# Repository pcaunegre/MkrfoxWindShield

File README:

This project includes several independant modules:

1. the hardware is an Arduino shield compatible with the MKRFOX1200 board.
 The shield provides an interface with wind sensors.
 3 types of wind sensors are compatible with this shield:
 --Davis
 --Peet Bros
 --Shenzen

2. the sofware to run the wind sensor and send measure to the OpenWindMap network

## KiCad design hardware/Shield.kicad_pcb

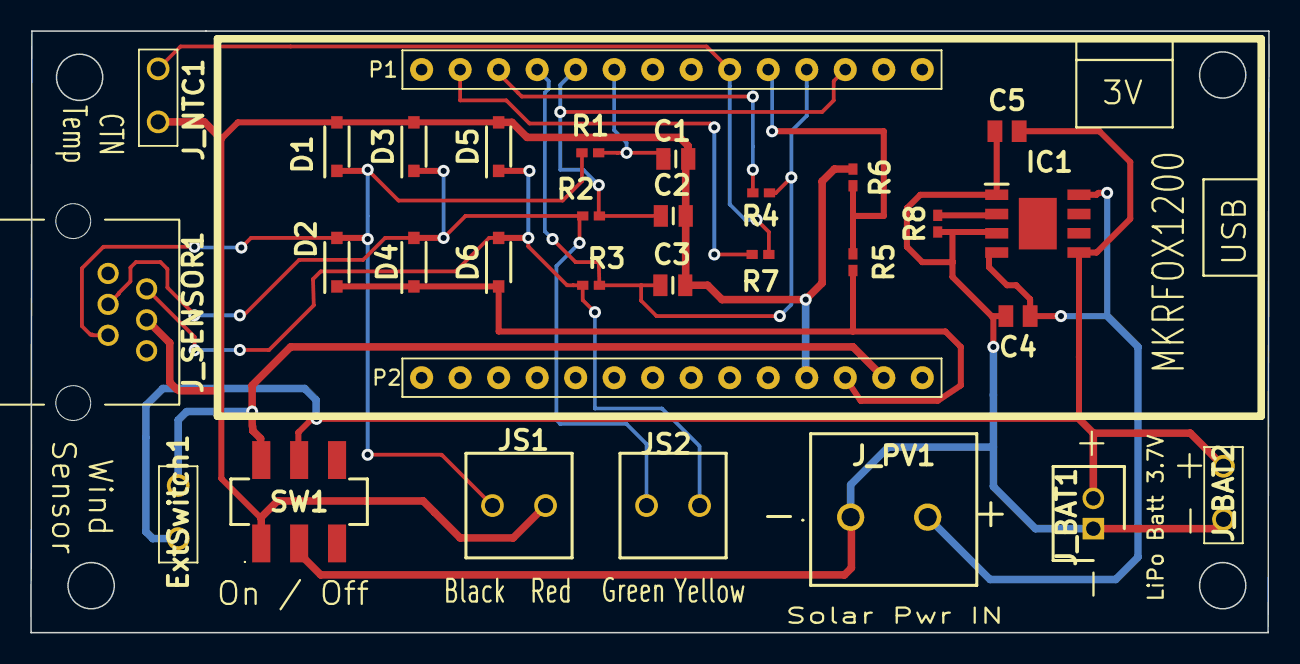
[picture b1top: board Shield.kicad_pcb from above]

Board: 2 copper layers, 81.6 x 39.7 mm, 31 parts (0 on the bottom side), 17 nets.

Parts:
C1, C2, C3: 10n; CAPC2012X65N
C4, C5: 10u; CAPC2012X140N
D1, D2, D3, D4, D5, D6: 1N5819W; SODFL3516X120N
ExtSwitch1: KF350-3.5-2P; SolderPoints
IC1: TP4056-42-ESOP8; SOIC127P600X175-9N
JS1, JS2: KF350-3.5-2P; KF350352P
J_BAT1: PH-2AK; SHDR2W52P0X200_1X2_600X460X630P
J_BAT2: KF350-3.5-2P; SolderPoints
J_NTC1: KF350-3.5-2P; SolderPoints
J_PV1: WJ500V-5.08-2P; WJ500V5082P
J_SENSOR1: DS1133-S60APS; DS1133S60APS
P1: CONN_14_1; CONN14_FP1
P2: CONN_14_2; CONN14_FP2
R1, R2, R3: 1K; RESC1005X40N
R4, R7: 10K; RESC1005X40N
R5: 390k; RESC1005X40N
R6: 100k; RESC1005X40N
R8: 20K; RESC1005X40N
SW1: JS202011SCQN

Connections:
A3: P1.A3, R5.2, R6.1
A4: J_NTC1.1, P1.A4, R7.2
D0: C1.2, P1.0, R1.2
D1A1: C2.2, P1.1, P1.A1, R2.2
D2A2: C3.2, P1.2, P1.A2, R3.2, R4.1
D3: P1.3, R4.2
D4: P1.4, R7.1
GND: C4.1, C5.1, IC1.1, IC1.3, J_BAT1.1, J_BAT2.2, J_PV1.1, R8.1, SW1.2
MGND: C1.1, C2.1, C3.1, D1.2, D3.2, D5.2, JS1.2, J_NTC1.2, J_SENSOR1.3, P2.GND, R6.2, SW1.1
unnamed: IC1.2, R8.2
VBAT: C5.2, ExtSwitch1.2, IC1.5, J_BAT1.2, J_BAT2.1, SW1.5
VCC: D2.1, D4.1, D6.1, P2.VCC, R5.1
VIN: ExtSwitch1.1, P2.VIN, SW1.6
VPV: C4.2, IC1.4, IC1.8, J_PV1.2
Wire1: D1.1, D2.2, JS1.1, J_SENSOR1.2, R1.1
Wire3: D3.1, D4.2, JS2.1, J_SENSOR1.4, R2.1
Wire4: D5.1, D6.2, JS2.2, J_SENSOR1.5, R3.1

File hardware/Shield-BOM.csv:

Comment,Designator,Footprint,LCSC,MFR part,
10nF ?10% 50V,"C1,C2,C3",0805,C1710 ,CL21B103KBANNNC,SMD
10uF ?10% 16V,"C4,C5",0805,C95841,CL21B106KOQNNNE,
Diode schottky 60V 1A ,"D1,D2,D3,D4,D5,D6",SOD-123,C110797,"PMEG6010CEH,115",
TP4056-42-ESOP8,IC1,ESOP-8_EP_3.9x4.9x1.27P,C16581,TP4056-42-ESOP8,
1k ?1% 1/16W,"R1,R2,R3",0402,C11702,0402WGF1001TCE,
10k 1/16W ?1% ,"R4,R7",0402,C25744,0402WGF1002TCE,
390k ?1% 1/16W,R5,0402,C25782,0402WGF3903TCE,
100k 1/16W ?1% ,R6,0402,C25741,0402WGF1003TCE,
20k 1/16W ?1%,R8,0402,C25765,0402WGF2002TCE,
Switch 6V 300mA ,SW1,SMD,C221666,JS202011SCQN,
P=3.5mm Screw terminal,"JS1,JS2",CONN-TH_P3.50_KF350-3.5-2P,C474892,KF350-3.5-2P,Hand soldered
2.54mm 14 Straight 1 Receptacle Through Hole,"P1,P2",HDR-TH_14P-P2.54-V,C124407,B-2200S14P-A120,
"2 Header PH 0.079""(2.00mm) Male Pin Through Hole Wire To Board",J_BAT1,CONN-TH_PH-2A,C8886,PH-2AK,
P=5.08mm Screw terminal ,J_PV1,CONN-TH_2P-P5.00_WJ500V-5.08-2P,C8465,WJ500V-5.08-2P,
DS1133-S60APS,J_SENSOR1,RJ11-TH_PCB-6P6C-90,C77857,DS1133-S60APS,
,,,,,
,J_NTC1,not mounted !!!,,,Not mounted

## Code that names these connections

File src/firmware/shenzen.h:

#define SHENZEN 30         // sensor number

#define ShenzenWire1  0    // wire1 (Black) to digital 0
//      ShenzenWire2       // wire2 (Red) to GND
#define ShenzenWire3  1    // wire3 (Yellow) to digital 1
#define ShenzenWire4  2    // wire4 (Green) to digital 2


#define ShenzenDirPin   A2  // analog direction - wire4 (Green)
#define ShenzenSpeedPin 1   // dig speed on D1  - wire3 (Yellow)

void Shenzen_setup();
void Shenzen_isr_speed();
int  Shenzen_takeWspeed(int deltaT);
int  Shenzen_takeWdir();

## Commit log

2021-11-05 project init
2021-11-07 measure working with davis
2021-11-08 shenzen sensor ok
2021-11-10 added sensor detection
2021-11-10 split code in several files
2021-11-15 parametrised thresholds
2021-11-18 started readme
2021-11-18 tuned detection, working for shenzen
2021-11-19 added peet, but not tested
2021-11-26 added vbat measure
2021-11-29 controling sensor power to save current
2021-11-29 added admin reccurent action
2021-12-01 preparing admin message
2021-12-01 created hardware schematics, started pcb
2021-12-02 completed PCB, DRC OK
2021-12-02 deleted unneeded file
2021-12-03 added grounded backplane
2021-12-03 fixed holes position
2021-12-03 added JLCPCB BOM file
2021-12-07 changed diode ref because missing in fab catalog
2021-12-21 validated sigfox dispatch, validated I consumption
2022-01-18 finished sensors, temperature, admin report
2022-01-18 doc added
2022-01-18 manual added
2022-01-19 revised manual
2022-01-20 more documentation
2022-01-20 minor doc details
2022-03-24 changed power on Davis, added debug control from pin11
2022-04-07 manual revised after code revision
2022-04-07 added usb serial reader python script
2022-04-13 fixed terrific bug on wind dir with Davis or Misol
2022-04-13 updated soft version
2022-04-21 reorg sockets
2022-04-21 Revert "updated soft version"
    This reverts commit ec333ab792278aeebab38000c117c2b14d257bda.
2022-04-22 modified hardware: position of sockets, points for external switch
2022-04-22 put the right code version
2022-05-04 doc update wrt hardware change
2022-10-28 little change to avoid compiler warning on char declaration
2022-11-08 fix timing overflow due to var type, added debug infos
2022-11-09 some code clean up
2022-11-21 utilities for getting admin report from OWM
2022-11-22 trying to fix admin report dispatch
2022-12-12 more printing features added to getAdminReport.py
2022-12-20 changed monitoring report and periodicity of msg
2023-01-20 fixing monitoring report
2023-01-21 comments added
2023-01-23 fixed bug on speed mini introduced in last commit
2023-05-02 minor change in getAdminReport.py script
2023-06-18 changed reboot time
2023-07-28 removed reboot on sigfox failure
2023-12-12 minor comment fix
2024-07-02 revision work on going
2024-07-15 minor changes on debug mode
2024-10-02 fixed readme
2024-10-28 fixed wiring schematic doc
